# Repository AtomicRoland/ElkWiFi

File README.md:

# Introduction

This project is a WiFi interface module for the Acorn Electron. It's a cartridge that fits into a Plus-1 socket. The cartridge contains a ROM for the necessary drivers and utility commands. There's also 128 kB paged RAM available for buffering and storing incoming data. The WiFi is handled by the famous ESP8266 module. This is controlled by a dual UART 16C2552.

# WARNINGS

## 1. Security
The Acorn Electron is in no way a secure device, nor is the software for the WiFi module. When using the commands or driver, usernames and passwords may be kept in memory.

## 2. Baud rate changes may brick the ESP8266
The default transmission speed for the ESP8266 is 115,200 baud. The Electron can handle data transfers at this speed. Do not try to change this speed because the ESP8266 might accept your command but does not always perform it correctly. You might end up with a module that communicates at an unknown serial speed. The only remedy to fix that is to flash the device (or replace it, after all, they cost only about £1.00).

# COMPATIBILITY

This cartridge is tested with an Acorn Electron and a standard Acorn Plus-1 expansion module. It is also tested with an Acorn Plus-1 and a Pres Plus-1 ROM. Both configurations work perfectly.

*Known issues:*
 * With a Pres AP6 ROM in a Plus-1 there is a slight corruption on the screen after a hard reset. The cartridge still works as expected.
 * The CPLD is configured to detect whether it is installed in a BBC Master computer. The software is written without using  Electron specific hardware and functions so it is expected to work in a BBC Master. However, this is not tested yet.
 * Neither is any compatibility tested with a disc system, the Tube and Econet interface. They probably won’t work correctly together.
 * This board clashes also with the AP5 extension for the Electron as both boards drive (part of) page &FC and page &FD.

# Useful commands

Command | Description
------- | -----------
DATE		|	display date
IFCFG	  |	display network information
JOIN		|	connect to a wireless network
LAP			| get a list of access points
LAPOPT	|	set options for lap command
LEAVE	  |	disconnect from current network
MODE		| select operating mode
PRD			| dump contents of paged ram
REWIND	|	reset UEF pointer
TIME		|	display current time
UPDATE	|	check for updates
VERSION	| display firmware information
WGET		|  retrieve a file from the Internet
WICFS		|  Activate WiCFS
WIFI		|	interface control

# Support

More information can be found in the manual in the doc directory. Please post your questions, remarks, compliments etc on the StarDot forum at https://stardot.org.uk/forums.

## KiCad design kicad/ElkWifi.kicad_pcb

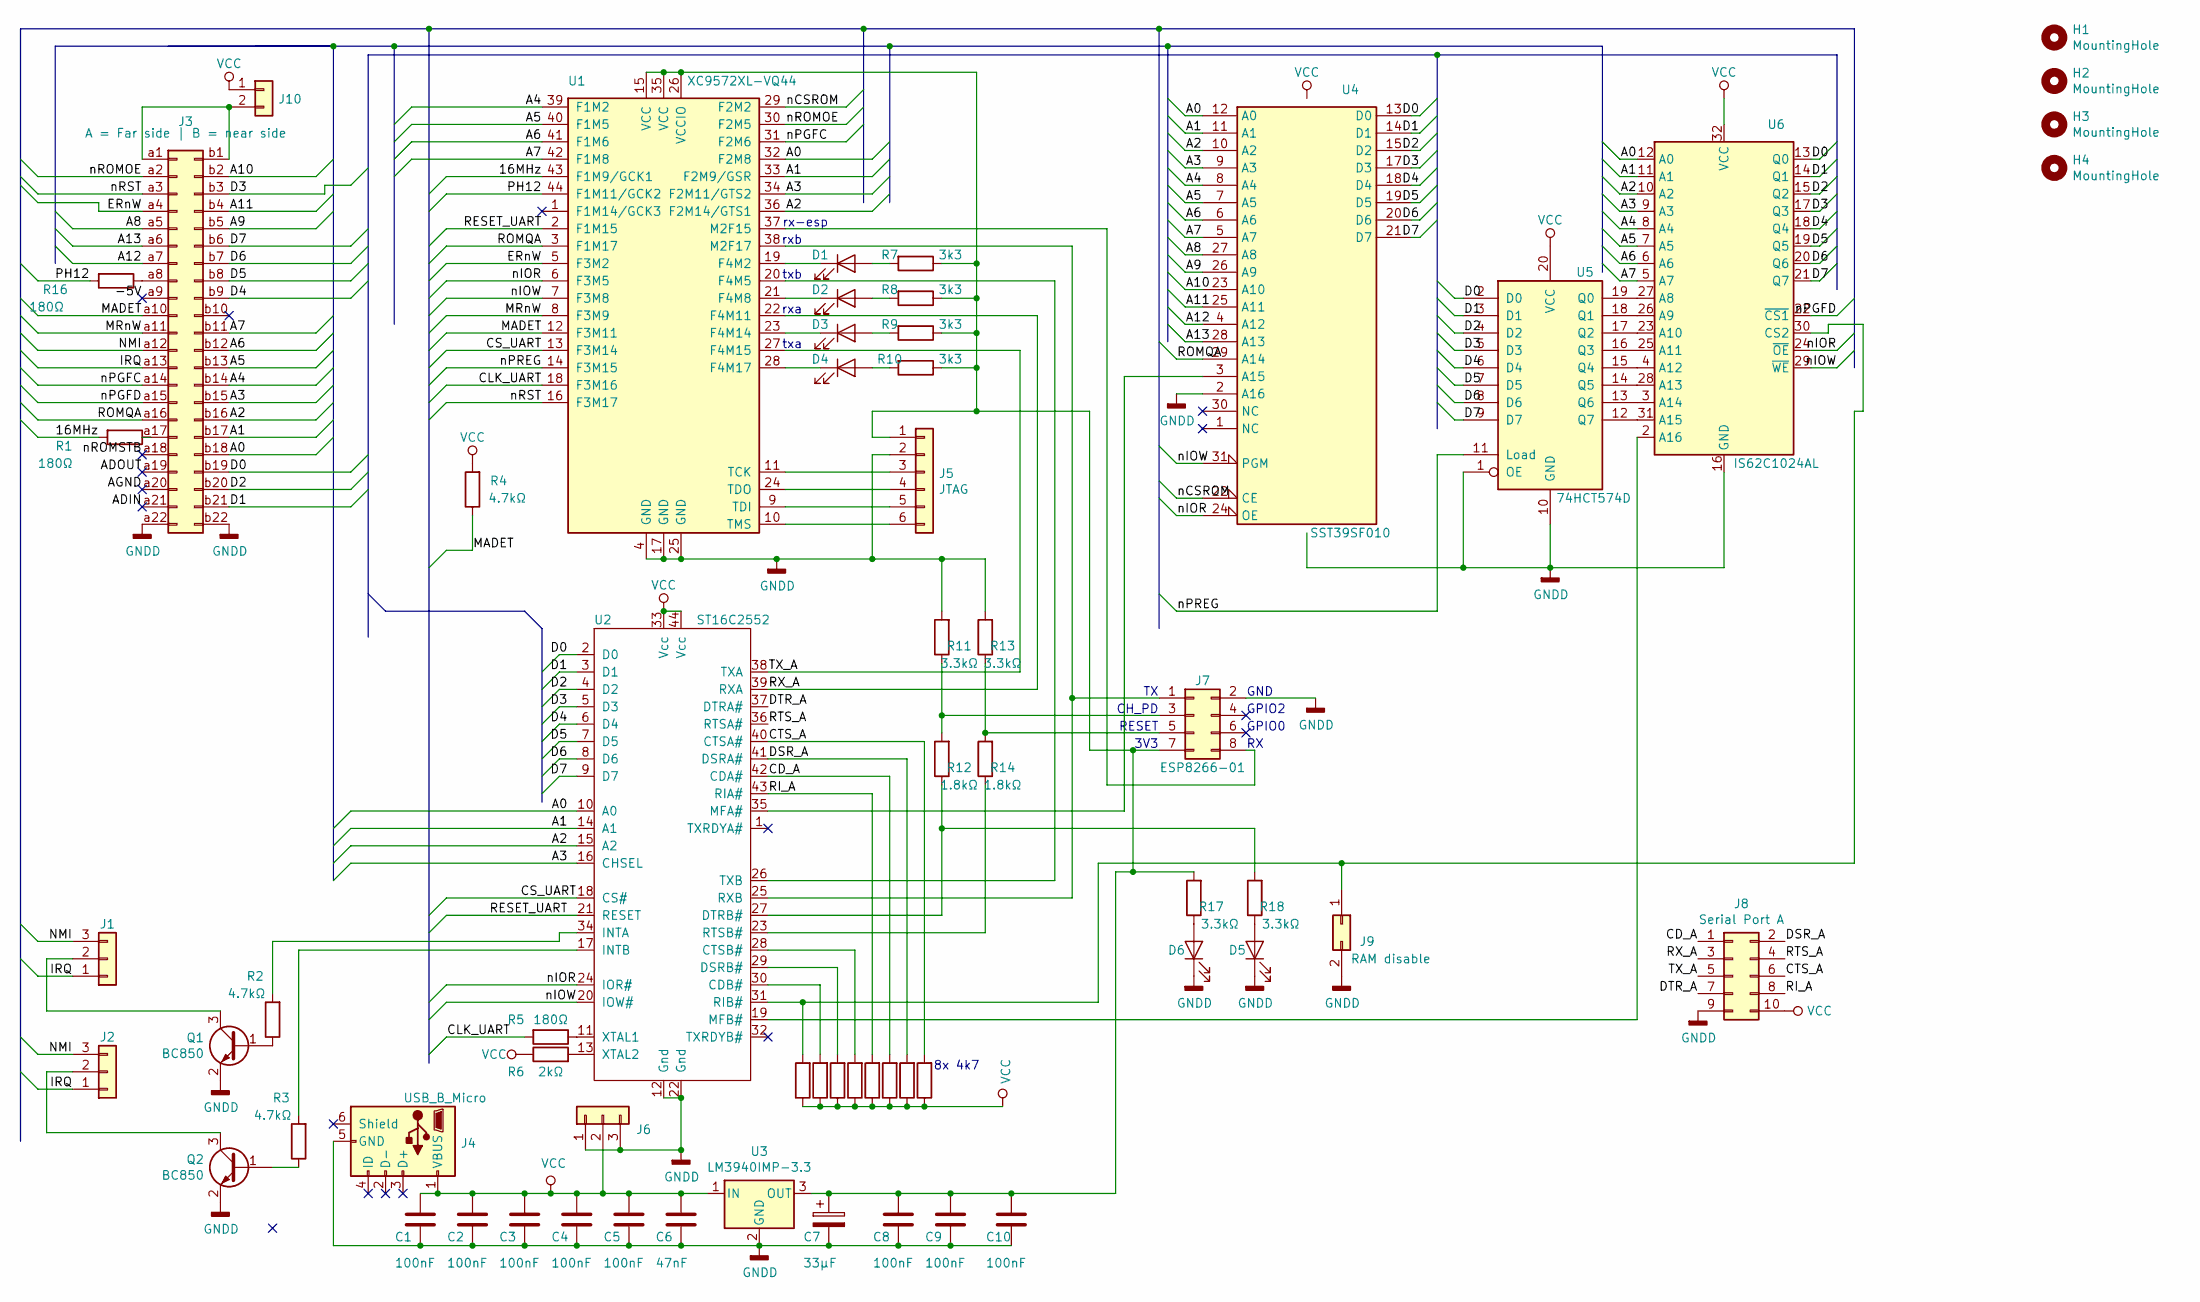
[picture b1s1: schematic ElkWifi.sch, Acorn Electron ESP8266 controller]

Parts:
C1, C2, C3, C4, C5, C8, C9, C10: 100nF; C_1206_3216Metric_Pad1.42x1.75mm_HandSolder
C6: 47nF; C_1206_3216Metric_Pad1.42x1.75mm_HandSolder
C7: 33µF; CP_Radial_D5.0mm_P2.50mm
D1, D2, D3, D4, D5, D6: LED; LED_D3.0mm
H1, H2, H3, H4: MountingHole; MountingHole_3.2mm_M3
J1: NMI / IRQ; PinHeader_1x03_P2.54mm_Vertical
J2, J6: Conn_01x03; PinHeader_1x03_P2.54mm_Vertical
J3: A = Far side | B = near side; acorn_electron_cartridge_edge_connector
J4: USB_B_Micro; USB_Mini-B_HX-series_Horizontal
J5: JTAG; PinHeader_1x06_P2.54mm_Vertical
J7: ESP8266-01; ESP8266-ESP-01
J8: Serial Port A; PinHeader_2x05_P2.54mm_Vertical
J9: RAM disable; PinHeader_1x02_P2.54mm_Vertical
J10: Conn_01x02; PinHeader_1x02_P2.54mm_Vertical
Q1, Q2: BC850; SOT-23
R1, R5, R16: 180Ω; R_1206_3216Metric_Pad1.42x1.75mm_HandSolder
R2, R3, R4, R15, R19, R20, R21, R22, R23, R24, R25: 4.7kΩ; R_1206_3216Metric_Pad1.42x1.75mm_HandSolder
R6: 2kΩ; R_1206_3216Metric_Pad1.42x1.75mm_HandSolder
R7, R8, R9, R10: 3k3; R_1206_3216Metric_Pad1.42x1.75mm_HandSolder
R11, R13, R17, R18: 3.3kΩ; R_1206_3216Metric_Pad1.42x1.75mm_HandSolder
R12, R14: 1.8kΩ; R_1206_3216Metric_Pad1.42x1.75mm_HandSolder
U1: XC9572XL-VQ44; TQFP-44_10x10mm_P0.8mm
U2: ST16C2552; PLCC-44_THT-Socket
U3: LM3940IMP-3.3; SOT-223-3_TabPin2
U4: SST39SF010; PLCC-32_THT-Socket
U5: 74HCT574D; SOIC-20W_7.5x12.8mm_P1.27mm
U6: IS62C1024AL; TSOP-II-32_21.0x10.2mm_P1.27mm

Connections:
/16MHz: R1.2, U1.43 (F1M9/GCK1)
/A0: J3.b18, U1.32 (F2M8), U2.10 (A0), U4.12 (A0), U6.12 (A0)
/A1: J3.b17, U1.33 (F2M9/GSR), U2.14 (A1), U4.11 (A1), U6.11 (A1)
/A2: J3.b16, U1.36 (F2M14/GTS1), U2.15 (A2), U4.10 (A2), U6.10 (A2)
/A3: J3.b15, U1.34 (F2M11/GTS2), U2.16 (CHSEL), U4.9 (A3), U6.9 (A3)
/A4: J3.b14, U1.39 (F1M2), U4.8 (A4), U6.8 (A4)
/A5: J3.b13, U1.40 (F1M5), U4.7 (A5), U6.7 (A5)
/A6: J3.b12, U1.41 (F1M6), U4.6 (A6), U6.6 (A6)
/A7: J3.b11, U1.42 (F1M8), U4.5 (A7), U6.5 (A7)
/A8: J3.a5, U4.27 (A8)
/A9: J3.b5, U4.26 (A9)
/A10: J3.b2, U4.23 (A10)
/A11: J3.b4, U4.25 (A11)
/A12: J3.a7, U4.4 (A12)
/A13: J3.a6, U4.28 (A13)
/CD_A: J8.1, R23.2, U2.42 (CDA#)
/CLK_UART: R5.2, U1.18 (F3M16)
/CS_UART: U1.13 (F3M14), U2.18 (CS#)
/CTS_A: J8.6, R25.2, U2.40 (CTSA#)
/D0: J3.b19, U2.2 (D0), U4.13 (D0), U5.2 (D0), U6.13 (Q0)
/D1: J3.b21, U2.3 (D1), U4.14 (D1), U5.3 (D1), U6.14 (Q1)
/D2: J3.b20, U2.4 (D2), U4.15 (D2), U5.4 (D2), U6.15 (Q2)
/D3: J3.b3, U2.5 (D3), U4.17 (D3), U5.5 (D3), U6.17 (Q3)
/D4: J3.b9, U2.6 (D4), U4.18 (D4), U5.6 (D4), U6.18 (Q4)
/D5: J3.b8, U2.7 (D5), U4.19 (D5), U5.7 (D5), U6.19 (Q5)
/D6: J3.b7, U2.8 (D6), U4.20 (D6), U5.8 (D6), U6.20 (Q6)
/D7: J3.b6, U2.9 (D7), U4.21 (D7), U5.9 (D7), U6.21 (Q7)
/DSR_A: J8.2, R24.2, U2.41 (DSRA#)
/DTR_A: J8.7, U2.37 (DTRA#)
/ERnW: J3.a4, U1.5 (F3M2)
/IRQ: J1.1, J2.1, J3.a13
/MADET: J3.a10, R4.1, U1.12 (F3M11)
/MRnW: J3.a11, U1.8 (F3M9)
/NMI: J1.3, J2.3, J3.a12
/PH12: R16.2, U1.44 (F1M11/GCK2)
/RESET_UART: U1.2 (F1M15), U2.21 (RESET)
/RI_A: J8.8, R22.2, U2.43 (RIA#)
/ROMQA: J3.a16, U1.3 (F1M17), U4.29 (A14)
/RTS_A: J8.4, U2.36 (RTSA#)
/RX_A: J8.3, U1.22 (F4M11), U2.39 (RXA)
/TX_A: J8.5, U1.27 (F4M15), U2.38 (TXA)
/nCSROM: U1.29 (F2M2), U4.22 (CE)
/nIOR: U1.6 (F3M5), U2.24 (IOR#), U4.24 (OE), U6.24 (~OE)
/nIOW: U1.7 (F3M8), U2.20 (IOW#), U4.31 (PGM), U6.29 (~WE)
/nPGFC: J3.a14, U1.31 (F2M6)
/nPGFD: J3.a15, U6.22 (~CS1)
/nPREG: U1.14 (F3M15), U5.11 (Load)
/nROMOE: J3.a2, U1.30 (F2M5)
/nRST: J3.a3, U1.16 (F3M17)
GND: C1.2, C2.2, C3.2, C4.2, C5.2, C6.2, C7.2, C8.2, C9.2, C10.2, D5.1 (K), D6.1 (K), J3.a22, J3.b22, J4.5 (GND), J5.2, J6.1, J6.3, J7.2, J8.9, J9.2, Q1.2 (E), Q2.2 (E), R11.2, R13.2, U1.4 (GND), U1.17 (GND), U1.25 (GND), U2.12 (Gnd), U2.22 (Gnd), U3.2 (GND), U4.2 (A16), U4.16 (GND), U5.1 (OE), U5.10 (GND), U6.16 (GND)
unnamed: C7.1, C8.1, C9.1, C10.1, J5.1, J7.7, R7.1, R8.1, R9.1, R10.1, R17.2, U1.15 (VCC), U1.26 (VCCIO), U1.35 (VCC), U3.3 (OUT)
unnamed: D1.1 (K), U1.19 (F4M2)
unnamed: D1.2 (A), R7.2
unnamed: D2.1 (K), U1.21 (F4M8)
unnamed: D2.2 (A), R8.2
unnamed: D3.1 (K), U1.23 (F4M14)
unnamed: D3.2 (A), R9.2
unnamed: D4.1 (K), U1.28 (F4M17)
unnamed: D4.2 (A), R10.2
unnamed: D5.2 (A), R18.1
unnamed: D6.2 (A), R17.1
unnamed: J1.2, Q1.3 (C)
unnamed: J2.2, Q2.3 (C)
unnamed: J3.a8, R16.1
unnamed: J3.a17, R1.1
unnamed: J5.3, U1.11 (TCK)
unnamed: J5.4, U1.24 (TDO)
unnamed: J5.5, U1.9 (TDI)
unnamed: J5.6, U1.10 (TMS)
unnamed: J7.1, U1.38 (M2F17), U2.25 (RXB)
unnamed: J7.3, R11.1, R12.2
unnamed: J7.5, R13.1, R14.2
unnamed: J7.8, U1.37 (M2F15)
unnamed: J9.1, R15.2, U2.31 (RIB#), U6.30 (CS2)
unnamed: J3.a1, J3.b1, J10.2
unnamed: Q1.1 (B), R2.1
unnamed: Q2.1 (B), R3.1
unnamed: R2.2, U2.34 (INTA)
unnamed: R3.2, U2.17 (INTB)
unnamed: R5.1, U2.11 (XTAL1)
unnamed: R6.2, U2.13 (XTAL2)
unnamed: R12.1, R18.2, U2.27 (DTRB#)
unnamed: R14.1, U2.23 (RTSB#)
unnamed: R19.2, U2.30 (CDB#)
unnamed: R20.2, U2.29 (DSRB#)
unnamed: R21.2, U2.28 (CTSB#)
unnamed: U1.20 (F4M5), U2.26 (TXB)
unnamed: U2.19 (MFB#), U6.2 (A16)
unnamed: U2.35 (MFA#), U4.3 (A15)
unnamed: U5.12 (Q7), U6.31 (A15)
unnamed: U5.13 (Q6), U6.3 (A14)
unnamed: U5.14 (Q5), U6.28 (A13)
unnamed: U5.15 (Q4), U6.4 (A12)
unnamed: U5.16 (Q3), U6.25 (A11)
unnamed: U5.17 (Q2), U6.23 (A10)
unnamed: U5.18 (Q1), U6.26 (A9)
unnamed: U5.19 (Q0), U6.27 (A8)
VCC: C1.1, C2.1, C3.1, C4.1, C5.1, C6.1, J4.1 (VBUS), J6.2, J8.10, J10.1, R4.2, R6.1, R15.1, R19.1, R20.1, R21.1, R22.1, R23.1, R24.1, R25.1, U2.33 (Vcc), U2.44 (Vcc), U3.1 (IN), U4.32 (VCC), U5.20 (VCC), U6.32 (VCC)

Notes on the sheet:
txa
rxa
txb
rxb
rx-esp
GND
GPIO2
GPIO0
3V3
RESET
CH_PD
8x 4k7

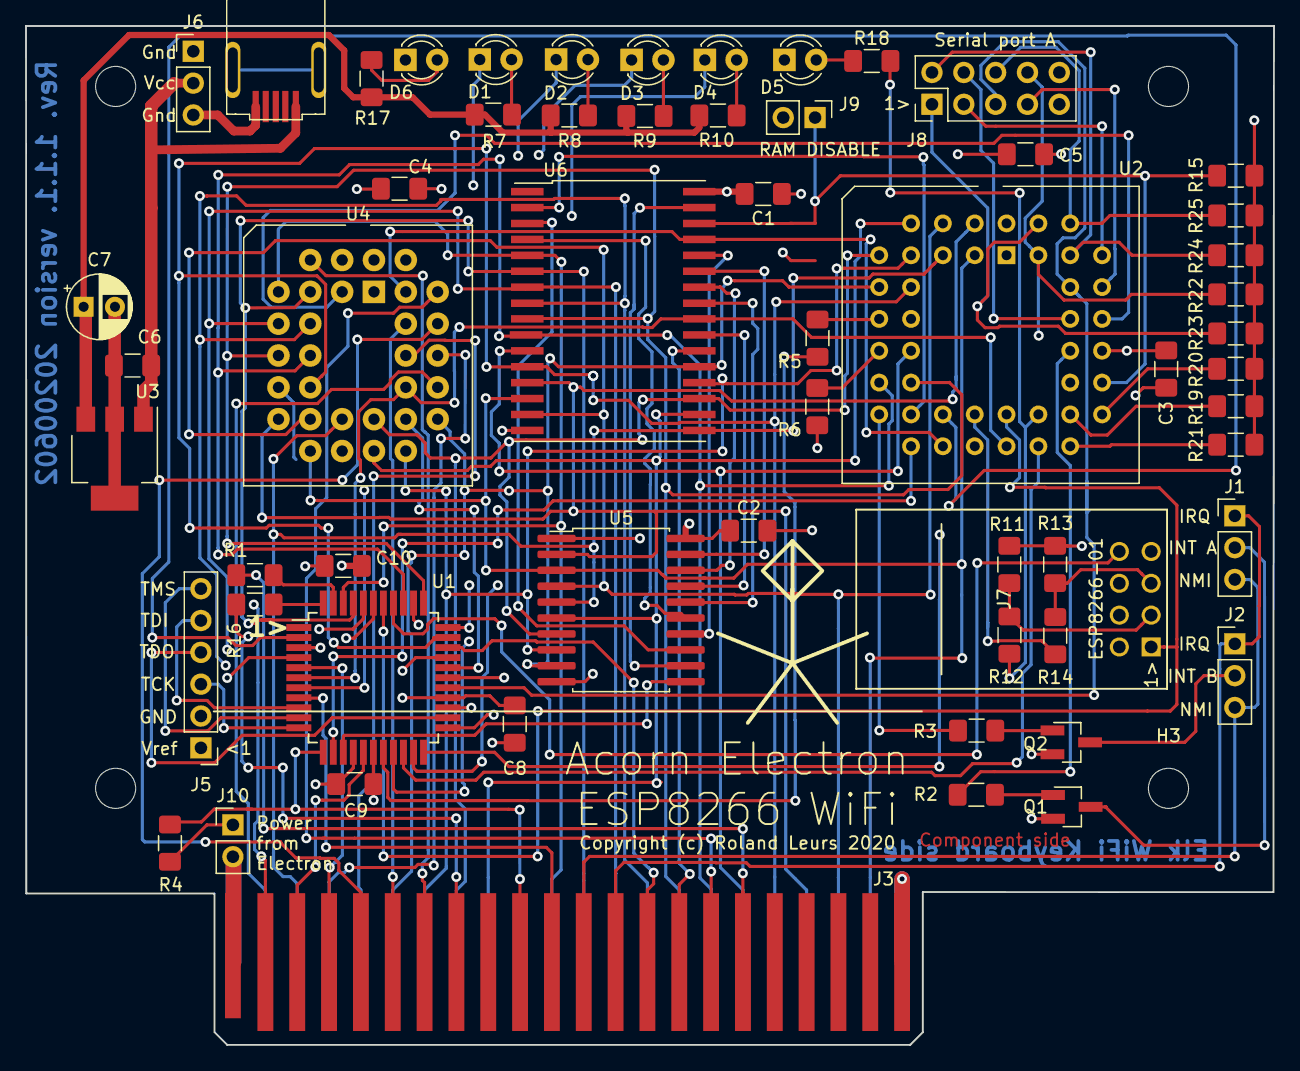
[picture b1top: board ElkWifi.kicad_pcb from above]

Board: 4 copper layers, 99.6 x 81.3 mm, 63 parts (0 on the bottom side), 98 nets.

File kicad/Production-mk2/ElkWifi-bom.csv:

Id;Designator;Quantity;Manufacturer;Manufacturer part number;Description / value;Package;Type
1;R22,R4,R3,R2,R15,R19,R20,R21,R23,R24,R25;11;YAGEO;RC1206JR-074K7L;Resistor 4.7kΩ;1206;SMD
2;R18,R17,R13,R11,R10,R9,R8,R7;8;MULTICOMP PRO;MCWF12P3301FTL;Resistor 3.3kΩ;1206;SMD
3;C6;1;MULTICOMP PRO;MC1206B473K101CT;Capacitor 47nF;1206;SMD
4;Q2,Q1;2;ON SEMICONDUCTOR;BC850CLT1G;Transistor BC850;SOT-23;SMD
5;R16,R5,R1;3;MULTICOMP PRO;MCPWR06FTEO1800;Resistor 180Ω;1206;SMD
6;U6;1;INTEGRATED SILICON SOLUTION (ISSI);IS62C1024AL-35QLI;Static RAM 128 Mbit IS62C1024AL;TSOP-II-32;SMD
7;U5;1;Nexperia;74HCT574D,653;8 bit latch 74HCT574D;SOIC-20;SMD
8;R14,R12,R6;3;TE CONNECTIVITY;CRGH1206F1K8;Resistor 1.8kΩ;1206;SMD
11;C10,C9,C8,C5,C4,C3,C2,C1;8;KEMET;C1206C104K1RACTU;Capacitor 100nF;1206;SMD
12;U1;1;Xilinx;XC9572XL-10VQG44C;CPLD XC9572XL-VQ44;TQFP-44;SMD
13;U3;1;Texas Instruments;LM3940IMP-3.3/NOPB;Voltage regulator LM3940IMP-3.3;SOT-223-3;SMD

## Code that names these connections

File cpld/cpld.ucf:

NET "PH12" BUFG=DATA_GATE;

NET "A(0)"            LOC = "P32";
NET "A(1)"            LOC = "P33";
NET "A(2)"            LOC = "P36";
NET "A(3)"            LOC = "P34";
NET "A(4)"            LOC = "P39";
NET "A(5)"            LOC = "P40";
NET "A(6)"            LOC = "P41";
NET "A(7)"            LOC = "P42";
NET "clk_in"          LOC = "P43";
NET "PH12"            LOC = "P44";
NET "ERnW"            LOC = "P5";
NET "MRnW"            LOC = "P8";

NET "madet"           LOC = "P12";
NET "nPGFC"           LOC = "P31";
NET "ROMQA"           LOC = "P3";
NET "nROMOE"          LOC = "P30";
NET "tx_a"            LOC = "P27";
NET "rx_a"            LOC = "P22";
NET "tx_b"            LOC = "P20";
NET "rx_b"            LOC = "P38";
NET "reset_in"        LOC = "P16";     
      
NET "cs_uart"         LOC = "P13";
NET "cs_rom"          LOC = "P29";
NET "cs_pareg"        LOC = "P14";
NET "ior"             LOC = "P6";
NET "iow"             LOC = "P7";
NET "clk_uart"        LOC = "P18";
NET "reset_out"       LOC = "P2";
NET "rx_esp"          LOC = "P37";
NET "LED_RX_A"        LOC = "P23";
NET "LED_TX_A"        LOC = "P28";
NET "LED_RX_B"        LOC = "P19";
NET "LED_TX_B"        LOC = "P21";

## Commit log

2020-08-07 Initial git repository. Working ROM and CPLD, however, they need just some adjustments before they can go into the public domain.
2020-08-07 Added KiCad files to git repository.
2020-08-08 *PRD command accepts second parameter for 64K bank selection ECHO OFF send to ESP8266 before each command Test for page ram availability at start of driver Test for wifi enabled at start of driver
2020-08-08 OSWORD call &65 implemented to call the WiFi driver from user applications.
2020-08-08 WGET modifications: - Bugfix after http header check - Test for connection error - Added -P for Atom-in-PC header
2020-08-09 Time-out setting integrated in driver and removed from * commands Changed receive data routine for hi-res graphics modes. It almost works.
2020-08-09 Moved the UART to address &FC3x to avoid clashes with AQR and DataCentre hardware Added write to MSR and LSR to block the reset for the UART, so the WiFi can stay disabled after a (hard) reset.
2020-08-13 Disable interrupts during receiving data from the ESP8266. This allows the WiFi to be used in high resulotion graphic modes.
2020-08-15 Inbetween commit during development of update command.
2020-08-15 Update of the EEPROM is now working. I just have to add the CRC check.
    The CRC of the server file will be added in the version file; the Elk
    must store it in memory before downloading the new bin-file.
2020-08-16 Added crc16 check to the update command. Also added the tools 'erase' and 'program' to manually reflash the EEPROM in case of emergency.
2020-08-18 Added the sources to match the definitive version; development system is also modified to have the correct memory assignments.
2020-08-21 Started with WiCFS
2020-08-21 Bugfix in prd when start address is not aligned to 0 or 8.
2020-08-21 Bugfix in join command where prompted password results in 'device not responding' error.
2020-08-24 Bugfixes: 1. Do not display the WiFi logo when WiFi is disabled 2. Perform a hard reset of the ESP8266 after power on
2020-08-24 Added the *DISCONNECT command to close a server connection that has been left open after an error condition. Close server connection in WGET when encountering a HTTP error or buffer full error.
2020-08-25 Revert "Added the *DISCONNECT command to close a server connection that has"
    This reverts commit fd1cf02e454bd15a709aaa01f7dae63ba0db5662.
2020-08-25 Revert "Revert "Added the *DISCONNECT command to close a server connection that has""
    This reverts commit 8de70a855ab3a591b1282e14a2c16042ed9a226e.
2020-08-25 Fixed the bug of the terminating &00 after the GET request header. Clear all ULA interrupts before enabling the interrupts after uart_read_response.
2020-09-01 Started alternative download
2020-09-02 Rewrite of read response for CIPSEND command. This is more stable because it is less dependent on timing of remote server.
2020-09-02 Removed writing to serial A port
2020-09-06 Added -S option to load a ROM image into sideways RAM. Updated version to 0.17
2020-09-06 Removed kicad files
2020-09-06 Added crc calculations for UPDATE command
2020-09-07 CPLD: Remove trailing white space
2020-09-07 CPLD: Fix cs_rom on Master
2020-09-07 CPLD: Fix clk_uart on Master
2020-09-07 Added incompatibility issue for WiCFS
2020-09-10 Added *MENU command
2020-09-12 Fixed broken update command.
2020-09-12 Removed debug command from *UPDATE Moved update server to acornelectron.nl Moved time server to acornelectron.nl
2020-09-12 Added release notes to *UPDATE (option -R)
2020-09-12 Set break type to 3 after loading a locked file
2020-09-13 Updated manual to version 0.20
2020-09-14 Started working on printer driver
2020-09-15 Added parsing serial data, there is an error in 24bit mul10 routine!
2020-09-17 Fixed the bug in MUL10 Added setup of serial port A
2020-09-18 Added copyright line Added license terms Corrected layout errors
2020-09-19 Added network printing routines. Not completely working yet.
2020-09-20 Added PING command
2020-09-21 Finished printing routine
2020-09-22 Updated the user manual with new commands (MENU, PING, PRINTER and SETSERIAL) New driver functions added (CIPMODE and PING) Corrected parameter text for CWMODE function in driver Added chapter about 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
2020-10-05 Two bugfixes: *LEAVE command was broken in v0.21 *UPDATE did not start update after pressing R to read release notes
2021-01-08 Update routines.asm
    Changed print_logo routine to use user-defined character to print instead of direct store in memory. Also added support for mode 7 display.
2021-01-09 Update flash.asm
    Check whether master ram board is present when jumping into reset routine in OS
2021-01-10 Update flash.asm
    Changed reset code to work with master ram board regardless of whether any other application has used the master ram flag at &27F.
2021-01-15 Update wget.asm
    Add support for second processor.
    If present data transfers will go to the second processor unless flags are set. The load address will default to PAGE (&800) unless supplied.
    A new flag F will force loading into the host processor. Any other flags will do the same.
    If the load address is >= &8000 it is a ROM and a run command will be sent to the second processor. Care must be taken that the correct load address is supplied, ie. usually &8000 or &B800. If it is 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
2021-01-16 Add second processor support to wget.asm (#4)
    * Update wget.asm
    * Update wget.asm
    * Update wget.asm
    * Update wget.asm
    * Update wget.asm
    * Update wget.asm
2021-01-26 Corrected some errors in the documentation.
2021-05-30 Update from version 0.23 to 0.26. I didn't push some updates inbetween those versions and I don't exactly remember what has changed. One important thing is that version 0.26 has some fixes to make it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
2021-06-06 Telnet in MODE 7 (simulator) in Prestel mode. Not quite good enough :-(
2021-06-07 Telnet in MODE 7 (simulator) in Prestel mode. Better, but still not quite good enough :-(
2021-09-15 Compatibility bugfix for *MENU command and ADFS.
2021-10-30 Added extra line feed in help text Fixed a bug that re-enables the WiFi after a reset
2022-03-22 Fixed markdown table
2022-03-22 Fixed markdown table (#5)
2022-03-26 Bugfix in serial_setup_a where due to a typo one register of the B port is addresses Feature: use spaces in parameters (e.g. network names) by using quotes.
2022-04-10 Updated documentation for using spaces in network name and other parameters.
2022-05-06 Feature request by John Kortink: * commands case insensitive
2022-11-04 Make command line case insensitive
2022-11-04 Added AP5 paged ram disable
2023-07-21 Implementing NTP by Timo Hartong
2023-07-23 Changed location of UTC Offset to &1FFFF in paged RAM Added -T to *UPDATE command to make UTC offset persistent
2023-07-29 Modified update command to support TI16C2552 UART. ROM imaged needs to be in lower ROM banks.
2023-09-16 Two minor text changes.
2023-09-17 Updated documentation with NTP information.
2023-09-26 Added driver function to set time out to allow slower servers. OSWORD&65 calls return with X and Y saved in &F0 and &F1.
2023-09-26 Documentation updated to version 0.32
2023-10-06 Add ROM files to gitignore
2023-10-06 Fix comment
2023-10-06 Add command options to select RAM bank
2023-10-08 Add documentation for new data option
2023-10-08 Fix cut and paste error in comment
2023-10-08 Fix comment typo
2023-10-08 Add google translate of comment
2023-10-09 Update help info with RAM bank selection option
2023-10-09 Set -D option to mimic -U option
2023-10-10 Initialise pointers for storing generic data in RAM bank 1
2023-10-11 Fix typo
2023-10-12 Use value not location
2023-10-12 Realyy make D the same as U
2023-10-15 Add build task to vscode project
2023-10-15 Update code to avoid using X register, which is reserved for use as the read buffer index.
2023-10-15 Move comments
2023-10-15 Set up data header
2023-10-15 Set data header values
2023-10-16 Remove vscode file from git
2023-10-16 Increase version number
2023-10-16 Update and re-layout documentation about new D option
2023-10-16 Add more comments
2023-11-14 Fix problem with ON ERROR being bypassed.
2023-11-15 Add error numbers and error table length check.
2023-11-18 Add data option (#7)
    * Add ROM files to gitignore
    * Fix comment
    * Add command options to select RAM bank
    * Add documentation for new data option
    * Fix cut and paste error in comment
    * Fix comment typo
2024-11-17 Firmware version 1.3.0.2 added
    Just in case you break your ESP module or get a module with an incompatible or broken firmware. Use the flash_esp.sh script on Linux to program the module. Requires esptool.py and a suitable programm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
2025-05-05 Fixed compatibility bug with RAMUTILS; multiplexing is now disabled in the WiFi driver (was never used anyways). Bugfix in calculating the end address of WGET -D option. Now &FD02/&FD03 point to firs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
2025-05-05 Documentation updated to version 0.34

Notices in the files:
kicad/ElkWifi.kicad_pcb:
Copyright (c) Roland Leurs 2020
